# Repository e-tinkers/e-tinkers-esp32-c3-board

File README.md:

# E-Tinkers ESP32-C3 Board

E-Tinkers ESP32-C3 Board is a ESP32-C3 dev board base on ESP32-C3-WROOM-02 module from  Expressif, unlike the official ESP-C3-DevKitM-1 or ESP32-C3-DevKitC-02, E-Tinkers ESP32-C3 Board does not has the USB Type-C port and the ESPLink on-board programmer, but it does include an on-board 600mA LDO and break out all the GPIO pins. It is designed for using as a WiFi/BLE shield or to integrated with another MCU and/or sensors, and before creating your own customizing design, you need an ESP32-C3 evaluation board for rapid prototype, in both cases USB port is probably not needed in the end product.

## Specification and Key features

Component|Detail |
----|----|
MCU         | 32-bit single-core RISC-V |
ROM         | 384KB |
SRAM        | 400KB(16KB for cache) |
Flash       | 4MB |
WiFi        | IEEE 802.11bgn |
Bluetooth   | BLE 5.0 & mesh |
GPIO        | 22 |
SPI         | 3 |
UART        | 2 |
I2C         | 1 |
RMT         | 2 Transmit + 2 Receive |
DMA         | 3 Transmit + 3 Receive |
LED-PWMC    | 6 channels |
TWAI        | 1 |
ADC         | 2 x 12bit, 6 channels |
Temp sensor | 1 |
Timer       | 6 |
Security    | OTP/AES/SHA/RSA/RNG/HMAC |

## Pin Assignements
All available GPIO pins of the ESP32-C3-WROOM-02 are broken out to the pin headers on the board.

## Firmware
Programming can be done using a USB-TTL Adaptor. The *Firmware* folder contains the firmware binary code , bootloader, and partition table for testing and demo purpose. Use [esptool](https://github.com/espressif/esptool) to upload the code to the board.

```
esptool.py --chip esp32c3 \
	--port /dev/cu.SLAB_USBtoUART \
	write_flash \
	--flash_mode dio \
	--flash_size 4MB \
	--flash_freq 80m \
	0x0 bootloader.bin \
	0x8000 partitions.bin \
	0x10000 firmware.bin
```

## Source Code
The source code for the firmware used can be found at this [repository](https://github.com/e-tinkers/esp32-c3-blinking).

## Reference
### esp-idf
https://github.com/espressif/esp-idf
### esp32-c3 get-started
https://docs.espressif.com/projects/esp-idf/en/latest/esp32c3/get-started/
### esp32-c3
https://www.espressif.com/en/products/socs/esp32-c3

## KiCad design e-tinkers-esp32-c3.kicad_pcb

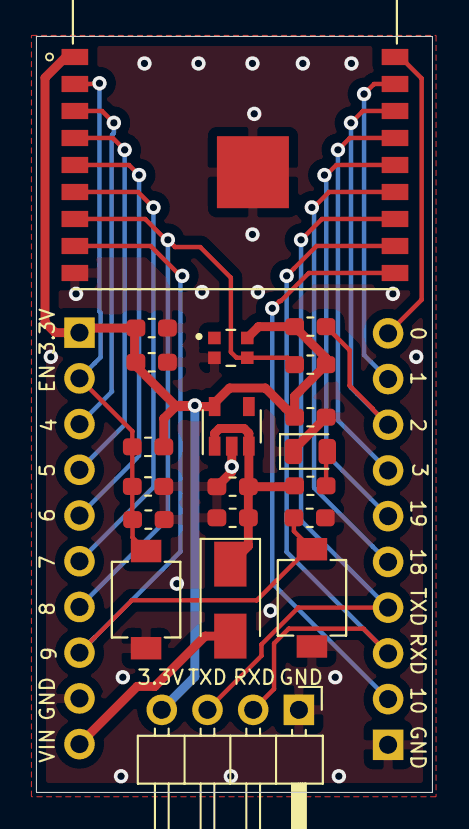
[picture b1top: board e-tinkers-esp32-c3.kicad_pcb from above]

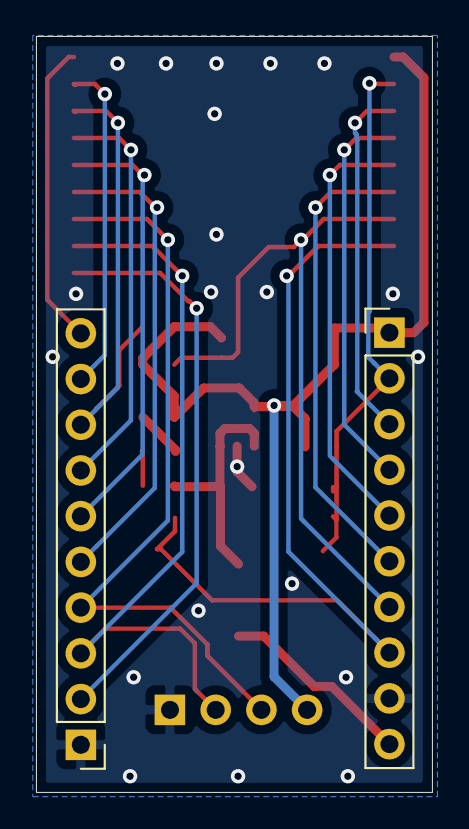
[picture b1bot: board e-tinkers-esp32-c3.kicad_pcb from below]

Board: 2 copper layers, 22.0 x 42.0 mm, 22 parts (2 on the bottom side), 21 nets.

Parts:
C1, C3, C4: 10uF; C_0603_1608Metric_Pad1.05x0.95mm_HandSolder
C2, C5, C6, C8: 0.1uF; C_0603_1608Metric_Pad1.05x0.95mm_HandSolder
C7: 1uF; C_0603_1608Metric_Pad1.05x0.95mm_HandSolder
D1: SS12; D_SMA
D2: LED_RED; LED_0805_2012Metric
J1, J2: Conn_01x10_Male; PinHeader_1x10_P2.54mm_Vertical
J3: Conn_01x04_Male; PinHeader_1x04_P2.54mm_Horizontal
R1: 2k; R_0603_1608Metric_Pad1.05x0.95mm_HandSolder
R2, R3, R5: 10k; R_0603_1608Metric_Pad1.05x0.95mm_HandSolder
SW1: RESET; SW_TS-1185-X-X
SW2: FLASH; SW_TS-1185-X-X
U1: AP2112K-3.3; SOT-23-5
U2: WS2812C-2020; LED_WS2812C-2020
U3: ESP32-C3-WROOM-02; MODULE_ESP32-C3-WROOM-02

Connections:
3.3V: C3.1, C4.1, C5.1, J1.1, J3.4, R2.1, R3.1, R5.1, U1.5, U2.4, U3.1
EN: C6.1, C7.1, J1.2, R5.2, SW1.2, U3.2
GND: C1.2, C2.2, C3.2, C4.2, C5.2, C6.2, C7.2, C8.2, D2.1, J1.9, J2.1, J3.1, SW1.1, SW2.1, U1.2, U2.2, U3.9, U3.19
IO0: J2.10, U3.18
IO1: J2.9, U3.17
IO2: J2.8, R3.2, U3.16
IO3: J2.7, U3.15
IO4: J1.3, U3.3
IO5: J1.4, U3.4
IO6: J1.5, U3.5
IO7: J1.6, U3.6
IO8: J1.7, R2.2, U2.3, U3.7
IO9: C8.1, J1.8, SW2.2, U3.8
IO10: J2.2, U3.10
IO18: J2.5, U3.13
IO19: J2.6, U3.14
unnamed: D2.2, R1.2
PWR: C1.1, C2.1, D1.1, R1.1, U1.1, U1.3
RXD: J2.3, J3.2, U3.11
TXD: J2.4, J3.3, U3.12
VIN: D1.2, J1.10

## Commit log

2021-10-24 inital commit
2021-10-24 add pinout diagram
2021-10-24 corect image url
2021-10-24 minor change on README
2021-11-16 minor update on README
2021-12-16 update firmware.bin for rgb_strip demo
2022-02-02 add link for source code
2024-04-28 update to kicad 6
